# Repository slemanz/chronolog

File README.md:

# Chronolog

## Overview

Chronolog is a temperature data logger built end to end, covering both hardware
and firmware. It records timestamped temperature readings to external flash and
shows live data on an LCD and over Wi-Fi.

📄 [View the schematic](hardware/schematic/chronolog.pdf)

## Repository Structure

- 🔌 **[hardware](hardware/):** KiCad project with schematic, PCB layout and
production files.
- 💾 **Firmware:** coming soon

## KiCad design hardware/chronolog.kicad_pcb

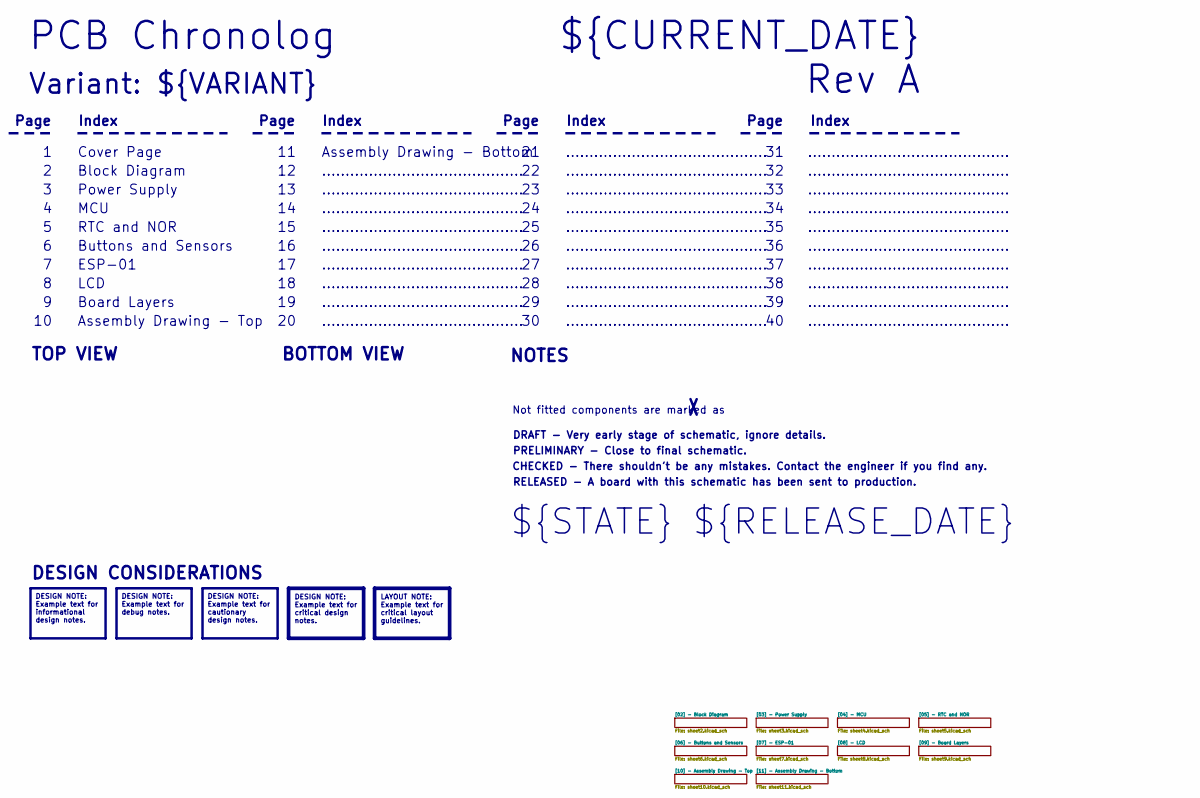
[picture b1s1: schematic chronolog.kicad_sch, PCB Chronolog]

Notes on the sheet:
Page
Not fitted components are marked as
...........................................
Index
RTC and NOR
BOTTOM VIEW
${STATE} ${RELEASE_DATE}
Board Layers
Rev ${REVISION}
DRAFT - Very early stage of schematic, ignore details.
ESP-01
Cover Page
MCU
NOTES
Variant: ${VARIANT}
PRELIMINARY - Close to final schematic.
LCD
DESIGN CONSIDERATIONS
Block Diagram
Assembly Drawing - Bottom
Assembly Drawing - Top
Buttons and Sensors
Power Supply
${CURRENT_DATE}
RELEASED - A board with this schematic has been sent to production.
${TITLE}
CHECKED - There shouldn't be any mistakes. Contact the engineer if you find any.
TOP VIEW
DESIGN NOTE: Example text for debug notes.
DESIGN NOTE: Example text for cautionary design notes.
LAYOUT NOTE: Example text for critical layout guidelines.
DESIGN NOTE: Example text for critical design notes.
DESIGN NOTE: Example text for informational design notes.

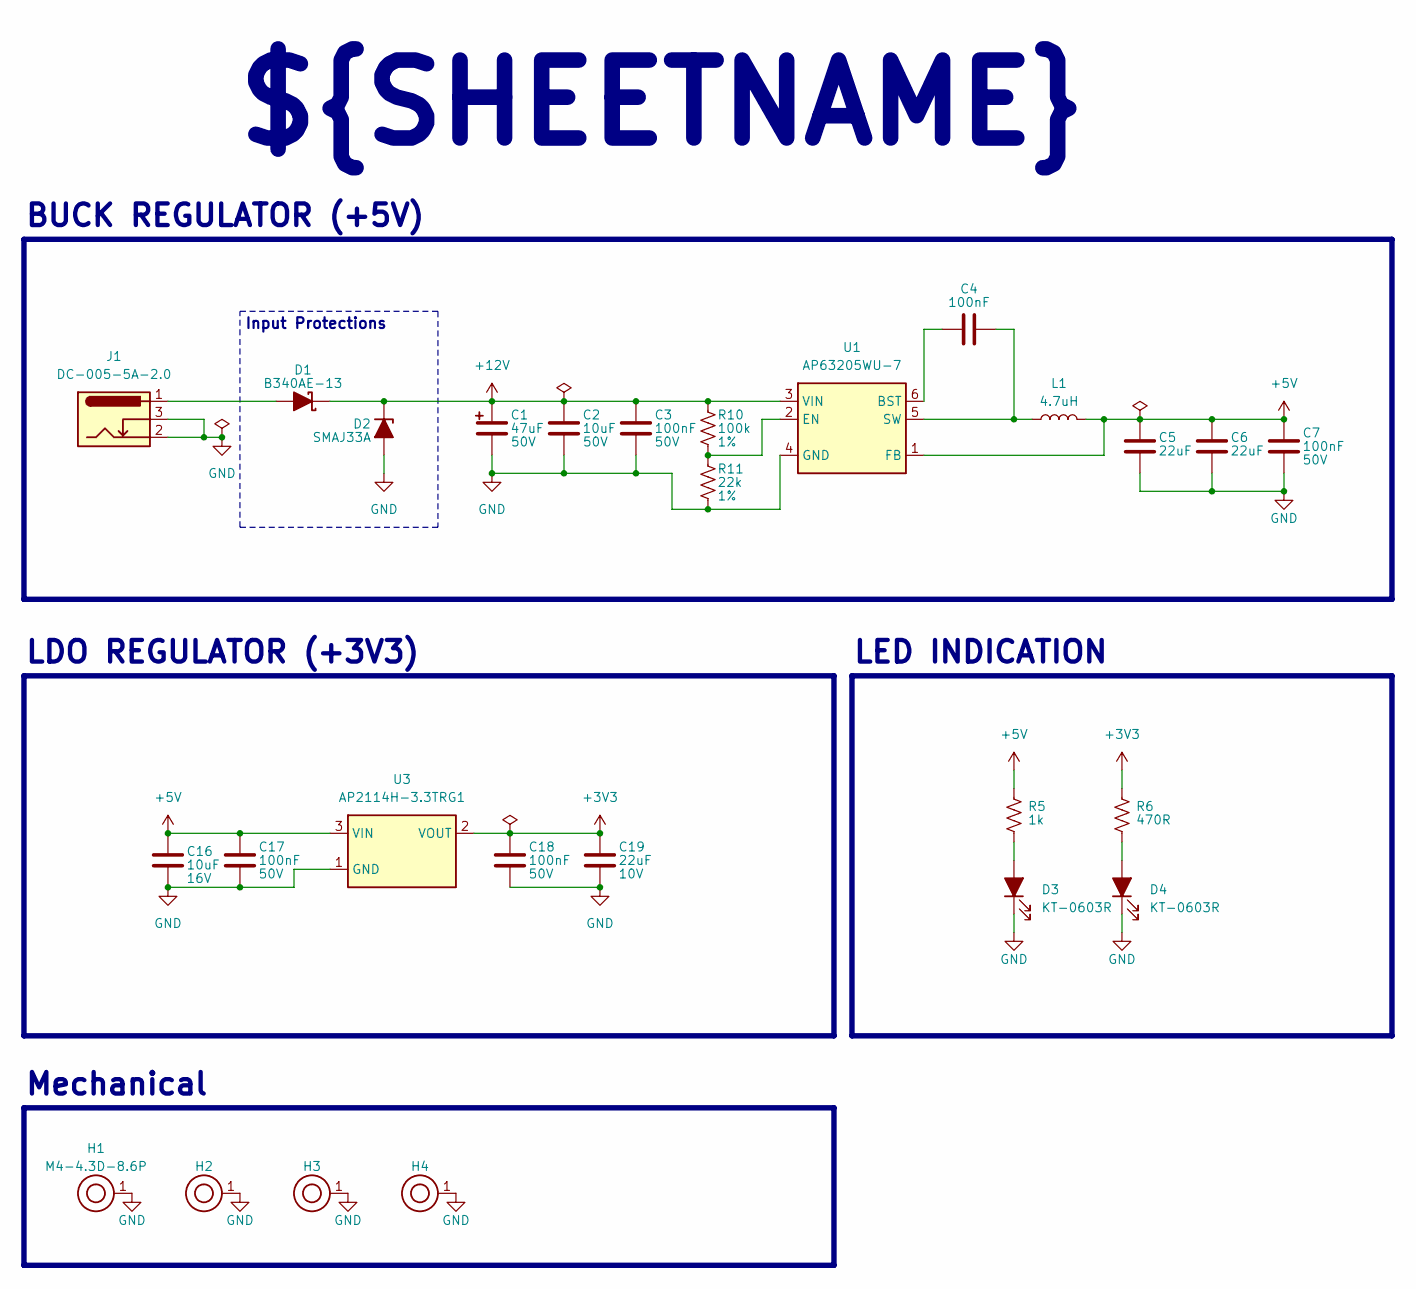
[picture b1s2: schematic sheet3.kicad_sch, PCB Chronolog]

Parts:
C1: 47uF; CP_Elec_6.3x5.8; Tolerance 20%; Voltage 50V; MPN VZT470M1HTT-0606L; LCSC C46682638
C2: 10uF; C_1210_3225Metric; Tolerance 10%; Voltage 50V; MPN GRM32ER71H106KA12L; LCSC C77102
C3, C4, C7, C17, C18: 100nF; C_0603_1608Metric; Tolerance 10%; Voltage 50V; MPN CC0603KRX7R9BB104; LCSC C14663
C5, C6: 22uF; C_1210_3225Metric; Tolerance 10%; Voltage 25V; MPN CL32B226KAJNNNE; LCSC C309062
C16: 10uF; C_0805_2012Metric; Tolerance 10%; Voltage 16V; MPN GRM21BR61C106KE15L; LCSC C77075
C19: 22uF; C_0805_2012Metric; Tolerance 20%; Voltage 10V; MPN GRM21BR61A226ME51L; LCSC C77074
D1: B340AE-13; D_SMA; MPN B340AE-13; LCSC C168859
D2: SMAJ33A; D_SMA; MPN SMAJ33A; LCSC C223988
D3, D4: KT-0603R; LED_0603_1608Metric; MPN KT-0603R; LCSC C2286
H1, H2, H3, H4: M4-4.3D-8.6P; MountingHole_4.3mm_M4_Pad
J1: DC-005-5A-2.0; TH_DC-005-5A-2.0; MPN DC-005-5A-2.0; LCSC C381116
L1: 4.7uH; L_1008_2520Metric; Tolerance 20%; MPN DFE252012F-4R7M=P2; LCSC C668313
R5: 1k; R_0603_1608Metric; Tolerance 1%; MPN 0603WAF1001T5E; LCSC C21190
R6: 470R; R_0603_1608Metric; Tolerance 1%; MPN 0603WAF4700T5E; LCSC C23179
R10: 100k; R_0603_1608Metric; Tolerance 1%; MPN 0603WAF1003T5E; LCSC C25803
R11: 22k; R_0603_1608Metric; Tolerance 1%; MPN 0603WAF2202T5E; LCSC C31850
U1: AP63205WU-7; TSOT-23-6; MPN AP63205WU-7; LCSC C2071056
U3: AP2114H-3.3TRG1; SOT-223-3_TabPin2; MPN AP2114H-3.3TRG1; LCSC C150716

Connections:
+3V3: C18.1, C19.1, R6.1, U3.2 (VOUT); also elsewhere on the board
+5V: C5.1, C6.1, C7.1, C16.1, C17.1, L1.2, R5.1, U1.1 (FB), U3.3 (VIN); also elsewhere on the board
+12V: C1.1, C2.1, C3.1, D1.1 (K), D2.1 (K), R10.1, U1.3 (VIN)
GND: C1.2, C2.2, C3.2, C5.2, C6.2, C7.2, C16.2, C17.2, C18.2, C19.2, D2.2 (A), D3.1 (K), D4.1 (K), H1.1, H2.1, H3.1, H4.1, J1.2, J1.3, R11.2, U1.4 (GND), U3.1 (GND); also elsewhere on the board
unnamed: D1.2 (A), J1.1
unnamed: D3.2 (A), R5.2
unnamed: D4.2 (A), R6.2
unnamed: C4.1, U1.6 (BST)
unnamed: R10.2, R11.1, U1.2 (EN)
unnamed: C4.2, L1.1, U1.5 (SW)

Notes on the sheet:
BUCK REGULATOR (+5V)
LED INDICATION
Input Protections
${SHEETNAME}
LDO REGULATOR (+3V3)
Mechanical

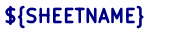
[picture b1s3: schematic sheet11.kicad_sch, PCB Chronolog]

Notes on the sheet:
${SHEETNAME}

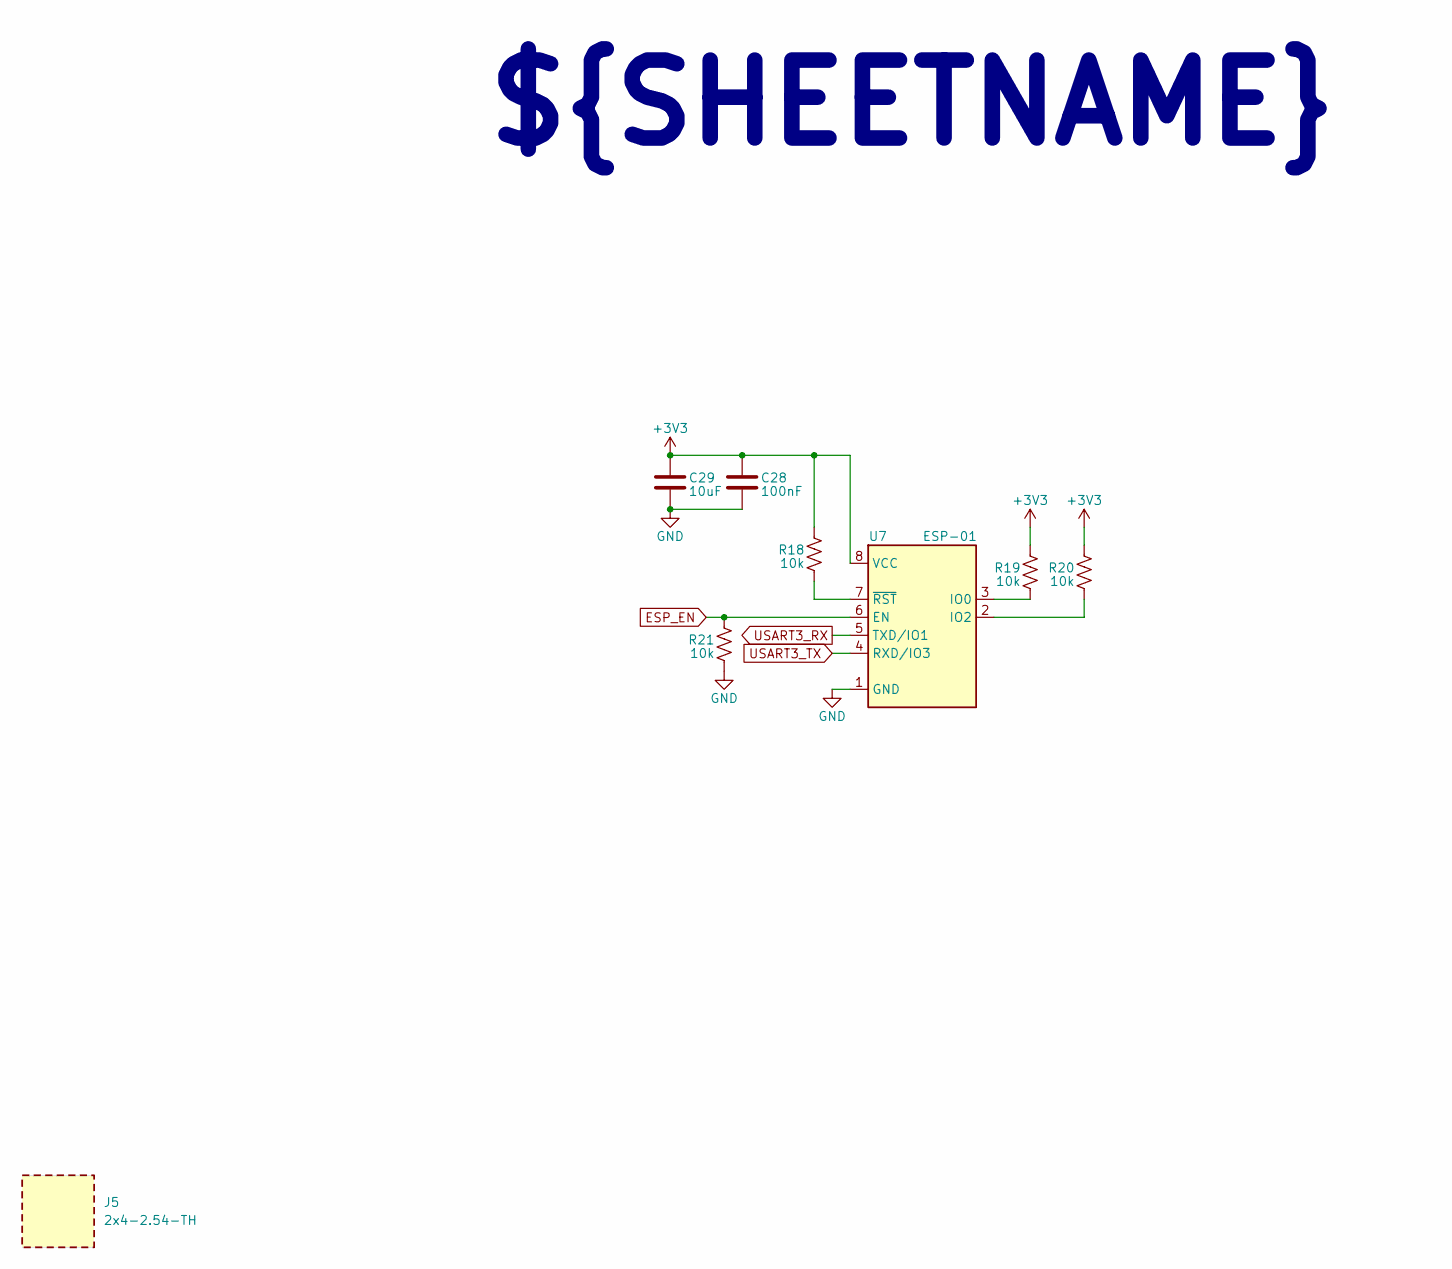
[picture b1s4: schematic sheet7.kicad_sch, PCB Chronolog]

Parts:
C28: 100nF; C_0603_1608Metric; Tolerance 10%; Voltage 50V; MPN CC0603KRX7R9BB104; LCSC C14663
C29: 10uF; C_0805_2012Metric; Tolerance 10%; Voltage 16V; MPN GRM21BR61C106KE15L; LCSC C77075
J5: 2x4-2.54-TH; MPN PM254-2-04-Z-8.5; LCSC C2897405
R18, R19, R20, R21: 10k; R_0603_1608Metric; Tolerance 1%; MPN 0603WAF1002T5E; LCSC C25804
U7: ESP-01; MPN ESP-01; LCSC C503581

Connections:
+3V3: C28.1, C29.1, R18.1, R19.1, R20.1, U7.8 (VCC); also elsewhere on the board
ESP_EN: R21.1, U7.6 (EN); also elsewhere on the board
GND: C28.2, C29.2, R21.2, U7.1 (GND); also elsewhere on the board
unnamed: R19.2, U7.3 (IO0)
unnamed: R20.2, U7.2 (IO2)
unnamed: R18.2, U7.7 (~RST)
USART3_RX: U7.5 (TXD/IO1); also elsewhere on the board
USART3_TX: U7.4 (RXD/IO3); also elsewhere on the board

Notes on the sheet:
${SHEETNAME}

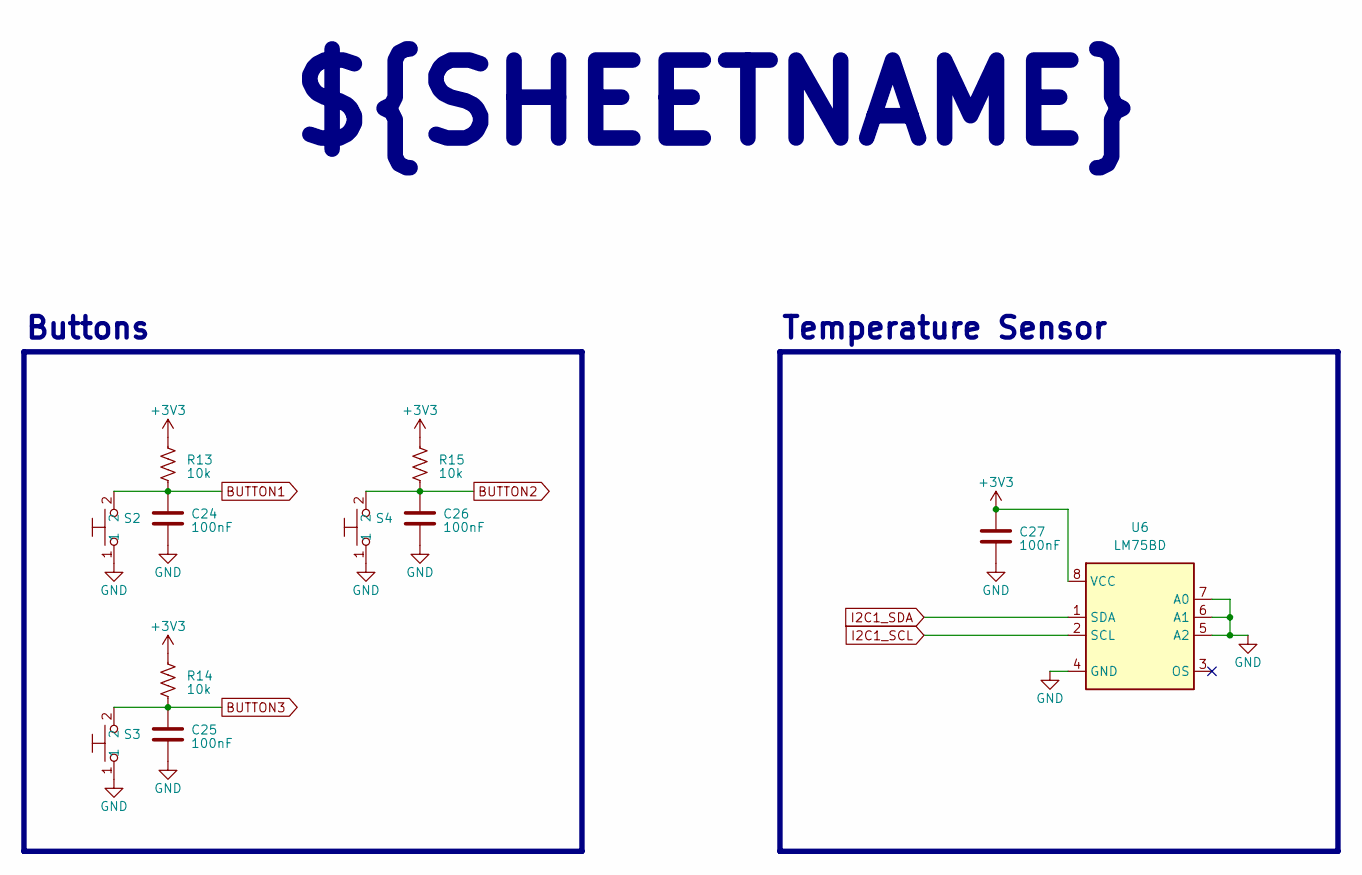
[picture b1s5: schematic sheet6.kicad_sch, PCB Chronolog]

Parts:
C24, C25, C26, C27: 100nF; C_0603_1608Metric; Tolerance 10%; Voltage 50V; MPN CC0603KRX7R9BB104; LCSC C14663
R13, R14, R15: 10k; R_0603_1608Metric; Tolerance 1%; MPN 0603WAF1002T5E; LCSC C25804
S2, S3, S4: TS-1088-AR02016; SW_SPST_TS-1088-xR020; MPN TS-1088-AR02016; LCSC C720477
U6: LM75BD; SOIC-8_3.9x4.9mm_P1.27mm; MPN LM75BD,118; LCSC C34565

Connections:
+3V3: C27.1, R13.1, R14.1, R15.1, U6.8 (VCC); also elsewhere on the board
BUTTON1: C24.1, R13.2, S2.2; also elsewhere on the board
BUTTON2: C26.1, R15.2, S4.2; also elsewhere on the board
BUTTON3: C25.1, R14.2, S3.2; also elsewhere on the board
GND: C24.2, C25.2, C26.2, C27.2, S2.1, S3.1, S4.1, U6.4 (GND), U6.5 (A2), U6.6 (A1), U6.7 (A0); also elsewhere on the board
I2C1_SCL: U6.2 (SCL); also elsewhere on the board
I2C1_SDA: U6.1 (SDA); also elsewhere on the board

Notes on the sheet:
Buttons
Temperature Sensor
${SHEETNAME}

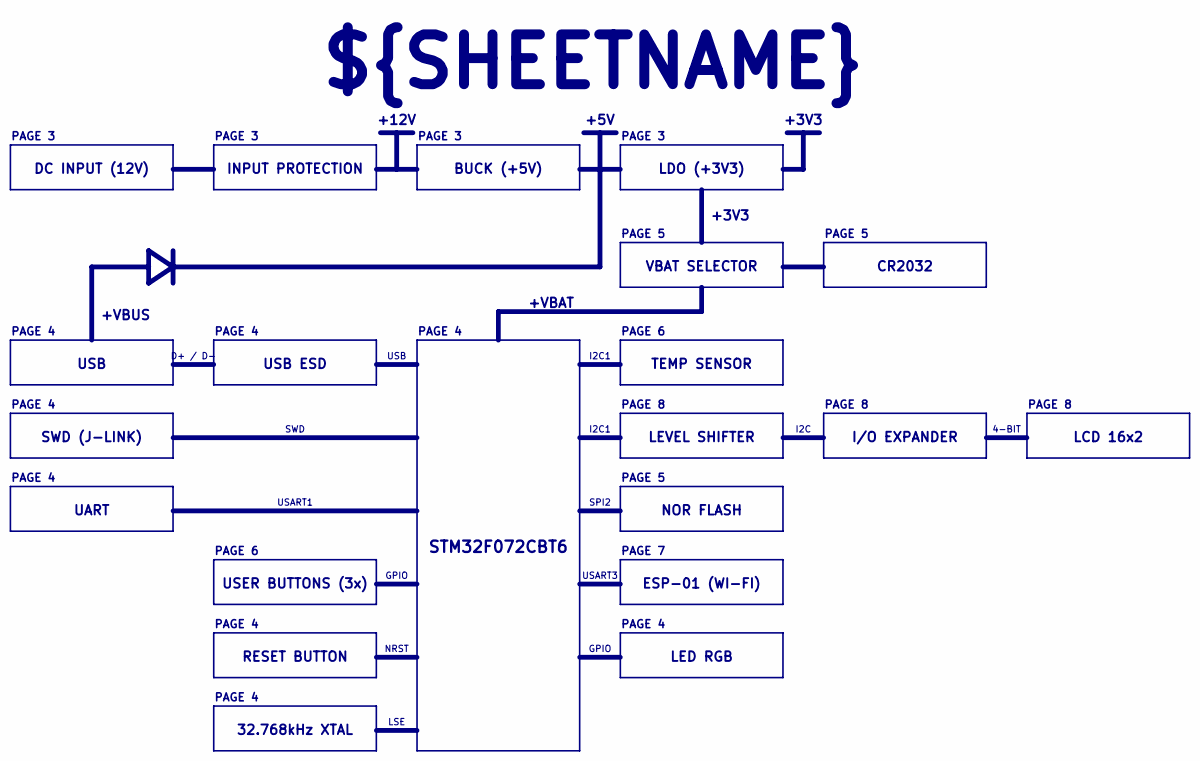
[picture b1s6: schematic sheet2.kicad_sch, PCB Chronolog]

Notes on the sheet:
PAGE 8
PAGE 3
+VBUS
NOR FLASH
SWD (J-LINK)
VBAT SELECTOR
USB ESD
NRST
PAGE 4
PAGE 6
+12V
INPUT PROTECTION
PAGE 5
DC INPUT (12V)
LED RGB
SPI2
LDO (+3V3)
UART
+5V
D+ / D-
+VBAT
CR2032
GPIO
I/O EXPANDER
USART1
+3V3
${SHEETNAME}
PAGE 7
32.768kHz XTAL
ESP-01 (WI-FI)
SWD
TEMP SENSOR
STM32F072CBT6
LSE
USB
USART3
4-BIT
I2C1
LEVEL SHIFTER
RESET BUTTON

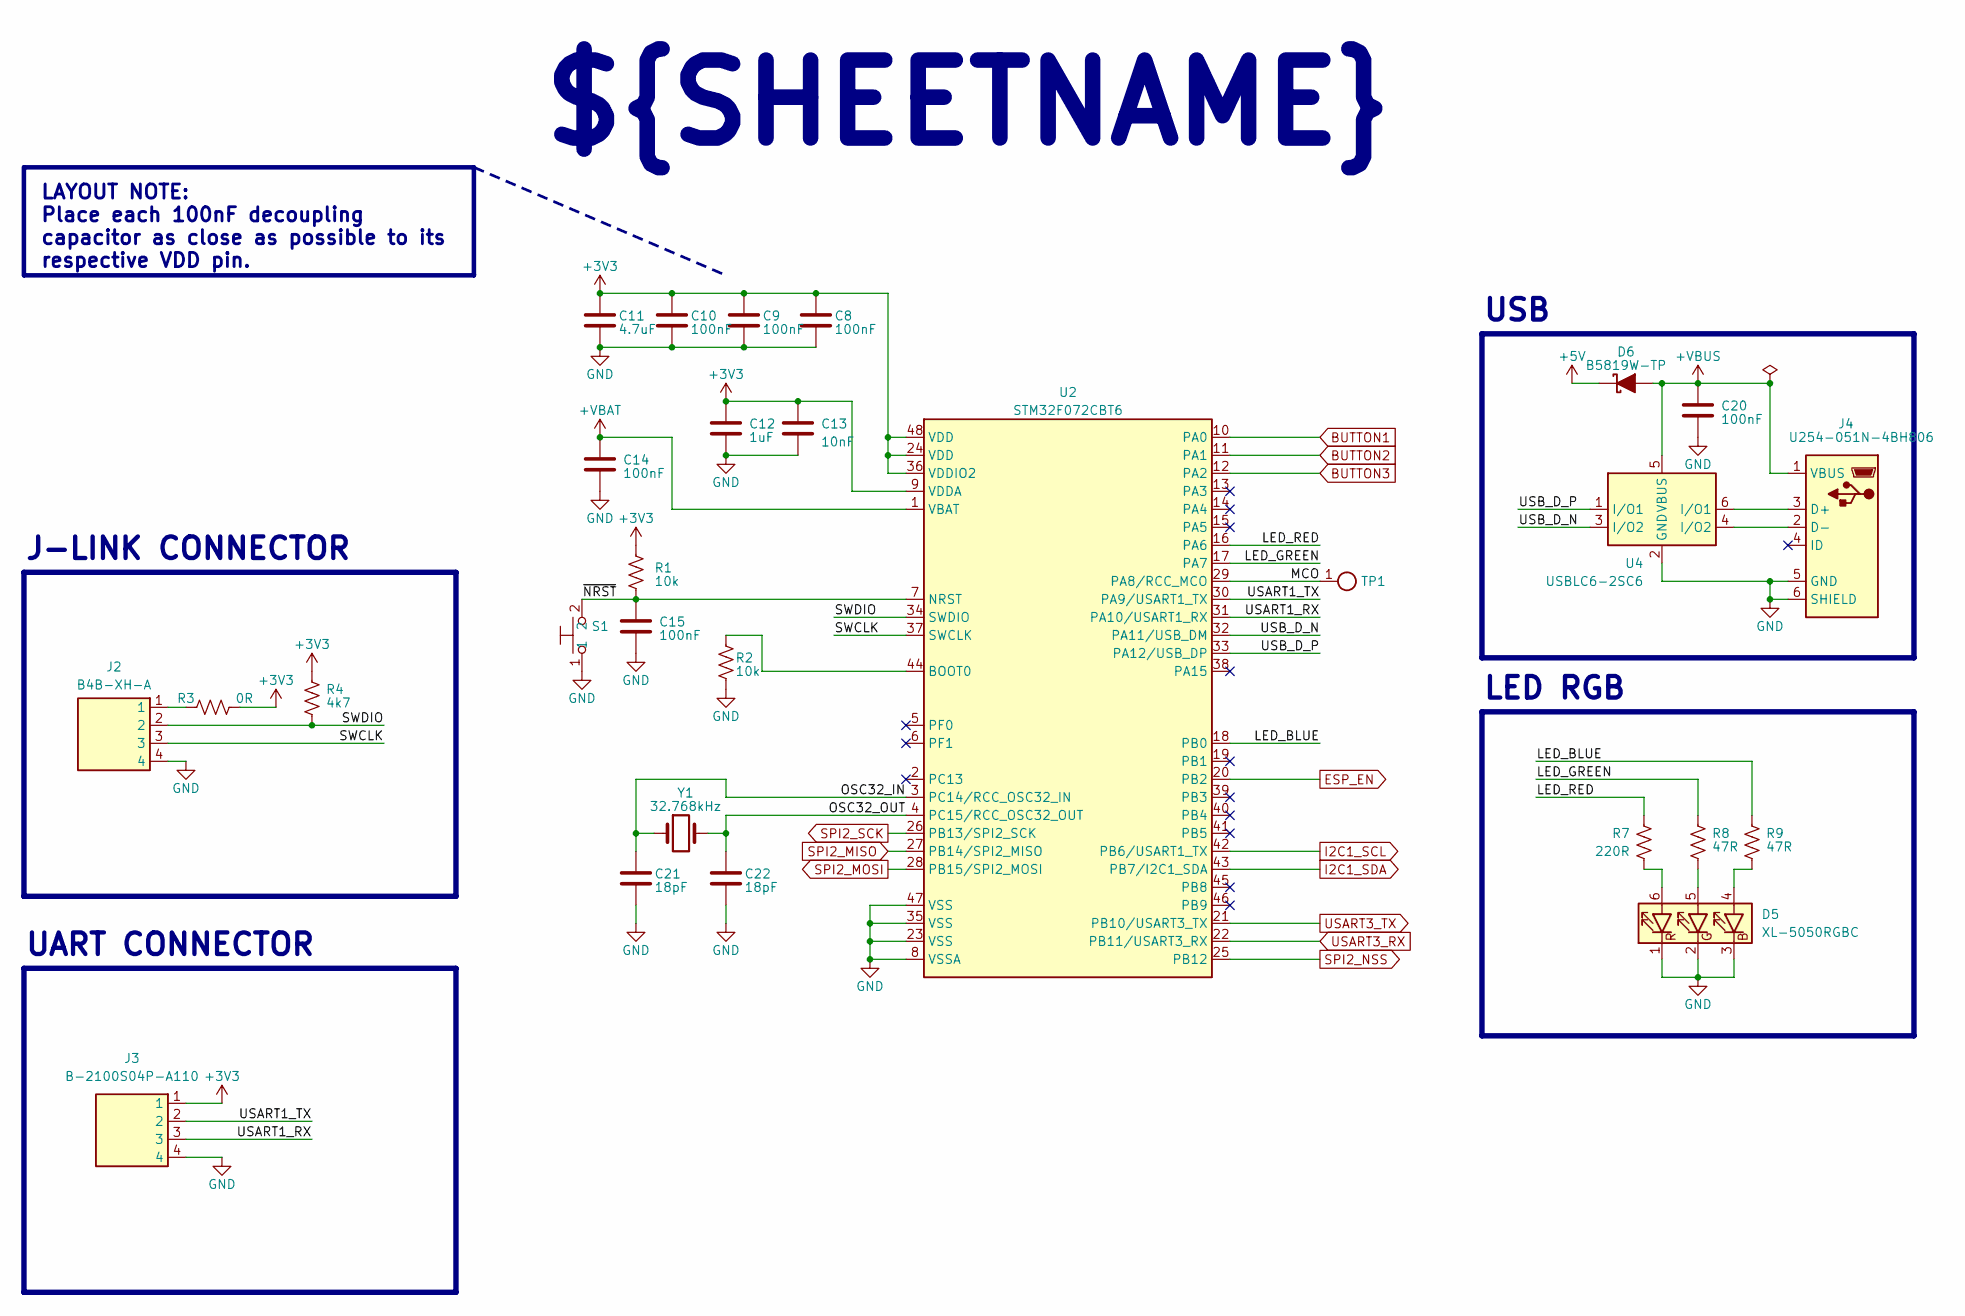
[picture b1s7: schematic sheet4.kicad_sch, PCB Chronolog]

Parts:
C8, C9, C10, C14, C15, C20: 100nF; C_0603_1608Metric; Tolerance 10%; Voltage 50V; MPN CC0603KRX7R9BB104; LCSC C14663
C11: 4.7uF; C_0603_1608Metric; Tolerance 10%; Voltage 16V; MPN GRM188R61C475KE11D; LCSC C77045
C12: 1uF; C_0603_1608Metric; Tolerance 10%; Voltage 25V; MPN GCM188R71E105KA64D; LCSC C85862
C13: 10nF; C_0603_1608Metric; Tolerance 10%; Voltage 50V; MPN 0603B103K500NT; LCSC C57112
C21, C22: 18pF; C_0603_1608Metric; Tolerance 5%; Voltage 50V; MPN CL10C180JB8NNNC; LCSC C1647
D5: XL-5050RGBC; PLCC-6_XL-5050RGBC; MPN XL-5050RGBC; LCSC C2843868
D6: B5819W-TP; D_SOD-123; MPN B5819W-TP; LCSC C84354
J2: B4B-XH-A; JST_XH_B4B-XH-A_1x04_P2.50mm_Vertical; MPN B4B-XH-A(LF)(SN); LCSC C144395
J3: B-2100S04P-A110; PinHeader_1x04_P2.54mm_Vertical; MPN B-2100S04P-A110; LCSC C124378
J4: U254-051N-4BH806; SMD_U254-051N-4BH806; MPN U254-051N-4BH806; LCSC C319170
R1, R2: 10k; R_0603_1608Metric; Tolerance 1%; MPN 0603WAF1002T5E; LCSC C25804
R3: 0R; R_0603_1608Metric; MPN 0603WAF0000T5E; LCSC C21189
R4: 4k7; R_0603_1608Metric; Tolerance 1%; MPN 0603WAF4701T5E; LCSC C23162
R7: 220R; R_0603_1608Metric; Tolerance 1%; MPN 0603WAF2200T5E; LCSC C22962
R8, R9: 47R; R_0603_1608Metric; Tolerance 1%; MPN 0603WAF470JT5E; LCSC C23182
S1: TS-1088-AR02016; SW_SPST_TS-1088-xR020; MPN TS-1088-AR02016; LCSC C720477
TP1: 1.0P-SMD; TestPoint_Pad_D1.0mm
U2: STM32F072CBT6; LQFP-48_7x7mm_P0.5mm; MPN STM32F072CBT6; LCSC C81720
U4: USBLC6-2SC6; SOT-23-6; MPN USBLC6-2SC6; LCSC C7519
Y1: 32.768kHz; Crystal_SMD_3215-2Pin_3.2x1.5mm; MPN Q13FC1350000400; LCSC C32346

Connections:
+3V3: C8.1, C9.1, C10.1, C11.1, C12.1, C13.1, J3.1, R1.1, R3.2, R4.1, U2.9 (VDDA), U2.24 (VDD), U2.36 (VDDIO2), U2.48 (VDD); also elsewhere on the board
+5V: D6.1 (K); also elsewhere on the board
+VBAT: C14.1, U2.1 (VBAT); also elsewhere on the board
+VBUS: C20.1, D6.2 (A), J4.1 (VBUS), U4.5 (VBUS)
/[04] - MCU/LED_BLUE: R9.1, U2.18 (PB0)
/[04] - MCU/LED_GREEN: R8.1, U2.17 (PA7)
/[04] - MCU/LED_RED: R7.1, U2.16 (PA6)
/[04] - MCU/MCO: TP1.1, U2.29 (PA8/RCC_MCO)
/[04] - MCU/OSC32_IN: C21.1, U2.3 (PC14/RCC_OSC32_IN), Y1.1
/[04] - MCU/OSC32_OUT: C22.1, U2.4 (PC15/RCC_OSC32_OUT), Y1.2
/[04] - MCU/SWCLK: J2.3, U2.37 (SWCLK)
/[04] - MCU/SWDIO: J2.2, R4.2, U2.34 (SWDIO)
/[04] - MCU/USART1_RX: J3.3, U2.31 (PA10/USART1_RX)
/[04] - MCU/USART1_TX: J3.2, U2.30 (PA9/USART1_TX)
/[04] - MCU/USB_D_N: U2.32 (PA11/USB_DM), U4.3 (I/O2)
/[04] - MCU/USB_D_P: U2.33 (PA12/USB_DP), U4.1 (I/O1)
/[04] - MCU/~NRST: C15.1, R1.2, S1.2, U2.7 (NRST)
BUTTON1: U2.10 (PA0); also elsewhere on the board
BUTTON2: U2.11 (PA1); also elsewhere on the board
BUTTON3: U2.12 (PA2); also elsewhere on the board
ESP_EN: U2.20 (PB2); also elsewhere on the board
GND: C8.2, C9.2, C10.2, C11.2, C12.2, C13.2, C14.2, C15.2, C20.2, C21.2, C22.2, D5.1 (RK), D5.2 (GK), D5.3 (BK), J2.4, J3.4, J4.5 (GND), J4.6 (SHIELD), R2.2, S1.1, U2.8 (VSSA), U2.23 (VSS), U2.35 (VSS), U2.47 (VSS), U4.2 (GND); also elsewhere on the board
I2C1_SCL: U2.42 (PB6/USART1_TX); also elsewhere on the board
I2C1_SDA: U2.43 (PB7/I2C1_SDA); also elsewhere on the board
unnamed: D5.4 (BA), R9.2
unnamed: D5.5 (GA), R8.2
unnamed: D5.6 (RA), R7.2
unnamed: J2.1, R3.1
unnamed: J4.3 (D+), U4.6 (I/O1)
unnamed: J4.2 (D-), U4.4 (I/O2)
unnamed: R2.1, U2.44 (BOOT0)
SPI2_MISO: U2.27 (PB14/SPI2_MISO); also elsewhere on the board
SPI2_MOSI: U2.28 (PB15/SPI2_MOSI); also elsewhere on the board
SPI2_NSS: U2.25 (PB12); also elsewhere on the board
SPI2_SCK: U2.26 (PB13/SPI2_SCK); also elsewhere on the board
USART3_RX: U2.22 (PB11/USART3_RX); also elsewhere on the board
USART3_TX: U2.21 (PB10/USART3_TX); also elsewhere on the board

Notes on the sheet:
LED RGB
USB
${SHEETNAME}
J-LINK CONNECTOR
UART CONNECTOR
LAYOUT NOTE: Place each 100nF decoupling capacitor as close as possible to its respective VDD pin.

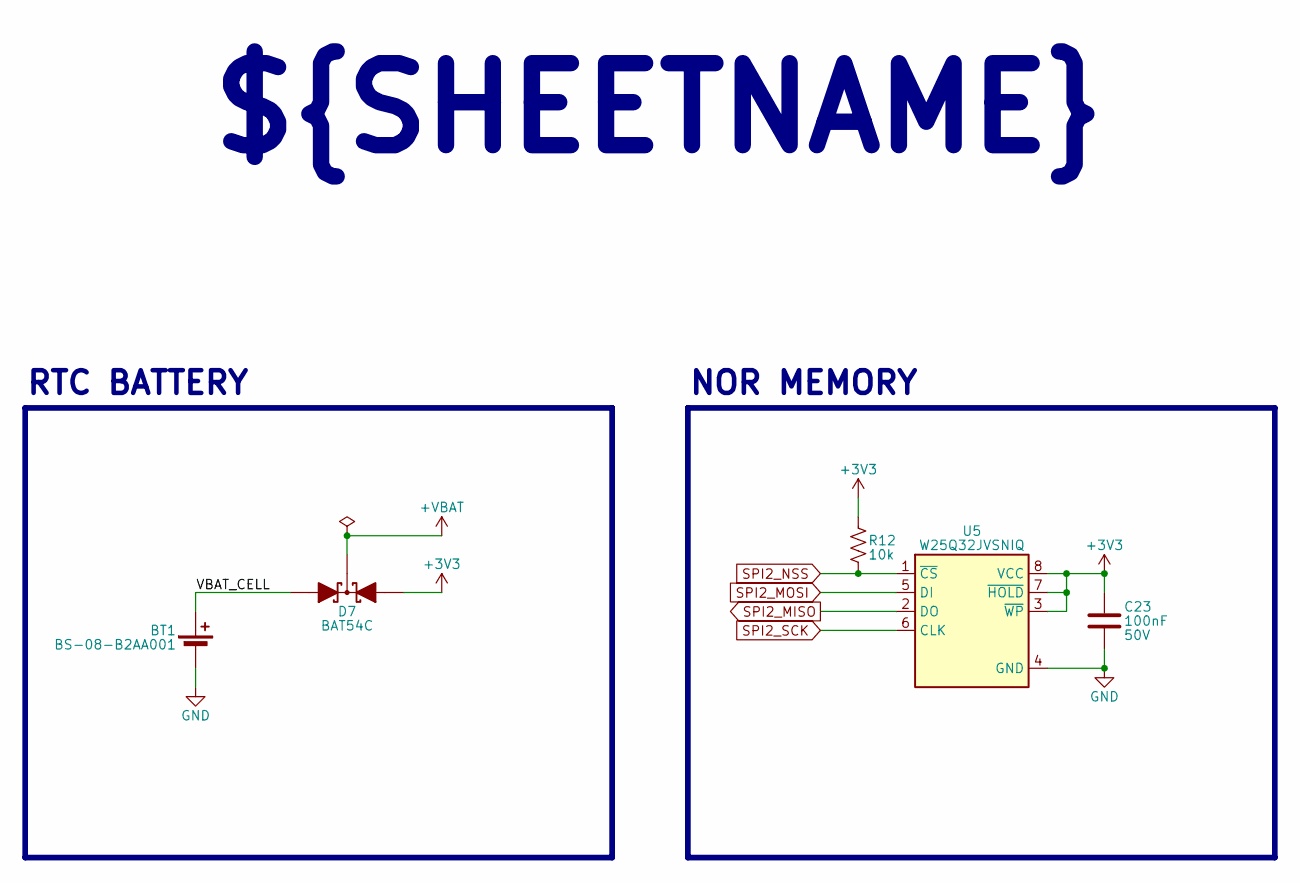
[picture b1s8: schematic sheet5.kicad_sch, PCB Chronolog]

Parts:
BT1: BS-08-B2AA001; SMD_BS-08-B2AA001; MPN BS-08-B2AA001; LCSC C964777
C23: 100nF; C_0603_1608Metric; Tolerance 10%; Voltage 50V; MPN CC0603KRX7R9BB104; LCSC C14663
D7: BAT54C; SOT-23; MPN BAT54C; LCSC C2135
R12: 10k; R_0603_1608Metric; Tolerance 1%; MPN 0603WAF1002T5E; LCSC C25804
U5: W25Q32JVSNIQ; SOIC-8_3.9x4.9mm_P1.27mm; MPN W25Q32JVSNIQ; LCSC C5355146

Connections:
+3V3: C23.1, D7.1 (A1), R12.1, U5.3 (~WP), U5.7 (~HOLD), U5.8 (VCC); also elsewhere on the board
+VBAT: D7.3 (K); also elsewhere on the board
/[05] - RTC and NOR/VBAT_CELL: BT1.1 (+), D7.2 (A2)
GND: BT1.2 (-), C23.2, U5.4 (GND); also elsewhere on the board
SPI2_MISO: U5.2 (DO); also elsewhere on the board
SPI2_MOSI: U5.5 (DI); also elsewhere on the board
SPI2_NSS: R12.2, U5.1 (~CS); also elsewhere on the board
SPI2_SCK: U5.6 (CLK); also elsewhere on the board

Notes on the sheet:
${SHEETNAME}
NOR MEMORY
RTC BATTERY

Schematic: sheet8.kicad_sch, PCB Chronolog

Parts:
C30, C31: 100nF; C_0603_1608Metric; Tolerance 10%; Voltage 50V; MPN CC0603KRX7R9BB104; LCSC C14663
J6: 1x16-2.54-TH; MPN KH-2.54FH-1X16P-H8.5; LCSC C2905421
P1: 1x16-2.54-TH; MPN B-2100S16P-A110; LCSC C49423290
Q1, Q2: BSS138; SOT-23; MPN BSS138; LCSC C52895
Q3: BC817-40LT1G; SOT-23; MPN BC817-40LT1G; LCSC C94412
R16, R17, R22, R25: 4k7; R_0603_1608Metric; Tolerance 1%; MPN 0603WAF4701T5E; LCSC C23162
R23: 1k; R_0603_1608Metric; Tolerance 1%; MPN 0603WAF1001T5E; LCSC C21190
R24: 10k; TH_3362P; Tolerance 10%; MPN 3362P-1-103LF; LCSC C58159
R26: 12R; R_0805_2012Metric; Tolerance 1%; MPN 0805W8F120JT5E; LCSC C17445
U8: WC1602A; MPN WC1602A; LCSC C5329588
U9: PCF8574T; SOIC-16W_7.5x10.3mm_P1.27mm; MPN PCF8574T; LCSC C7605

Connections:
+3V3: Q1.1 (G), Q2.1 (G), R16.1, R17.1; also elsewhere on the board
+5V: C30.1, C31.1, R22.1, R24.3, R25.1, R26.1, U8.2 (VDD), U9.16 (VDD); also elsewhere on the board
/[08] - LCD/LCD_BL: R23.1, U9.7 (P3)
/[08] - LCD/LCD_D4: U8.11 (D4), U9.9 (P4)
/[08] - LCD/LCD_D5: U8.12 (D5), U9.10 (P5)
/[08] - LCD/LCD_D6: U8.13 (D6), U9.11 (P6)
/[08] - LCD/LCD_D7: U8.14 (D7), U9.12 (P7)
/[08] - LCD/LCD_EN: U8.6 (E), U9.6 (P2)
/[08] - LCD/LCD_RS: U8.4 (RS), U9.4 (P0)
/[08] - LCD/LCD_RW: U8.5 (R/W), U9.5 (P1)
/[08] - LCD/LCD_SCL: Q1.3 (D), R25.2, U9.14 (SCL)
/[08] - LCD/LCD_SDA: Q2.3 (D), R22.2, U9.15 (SDA)
GND: C30.2, C31.2, Q3.2 (E), R24.1, U8.1 (VSS), U9.1 (A0), U9.2 (A1), U9.3 (A2), U9.8 (GND); also elsewhere on the board
I2C1_SCL: Q1.2 (S), R17.2; also elsewhere on the board
I2C1_SDA: Q2.2 (S), R16.2; also elsewhere on the board
unnamed: Q3.1 (B), R23.2
unnamed: Q3.3 (C), U8.16 (LED(-))
unnamed: R26.2, U8.15 (LED(+))
unnamed: R24.2, U8.3 (VO)

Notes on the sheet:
${SHEETNAME}

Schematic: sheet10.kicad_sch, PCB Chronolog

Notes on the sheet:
${SHEETNAME}

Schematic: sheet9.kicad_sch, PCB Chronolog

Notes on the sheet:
IN1
${SHEETNAME}
BOTTOM
TOP
IN2
DESIGN NOTE: All layers are viewed from the top side of the board (not mirrored).

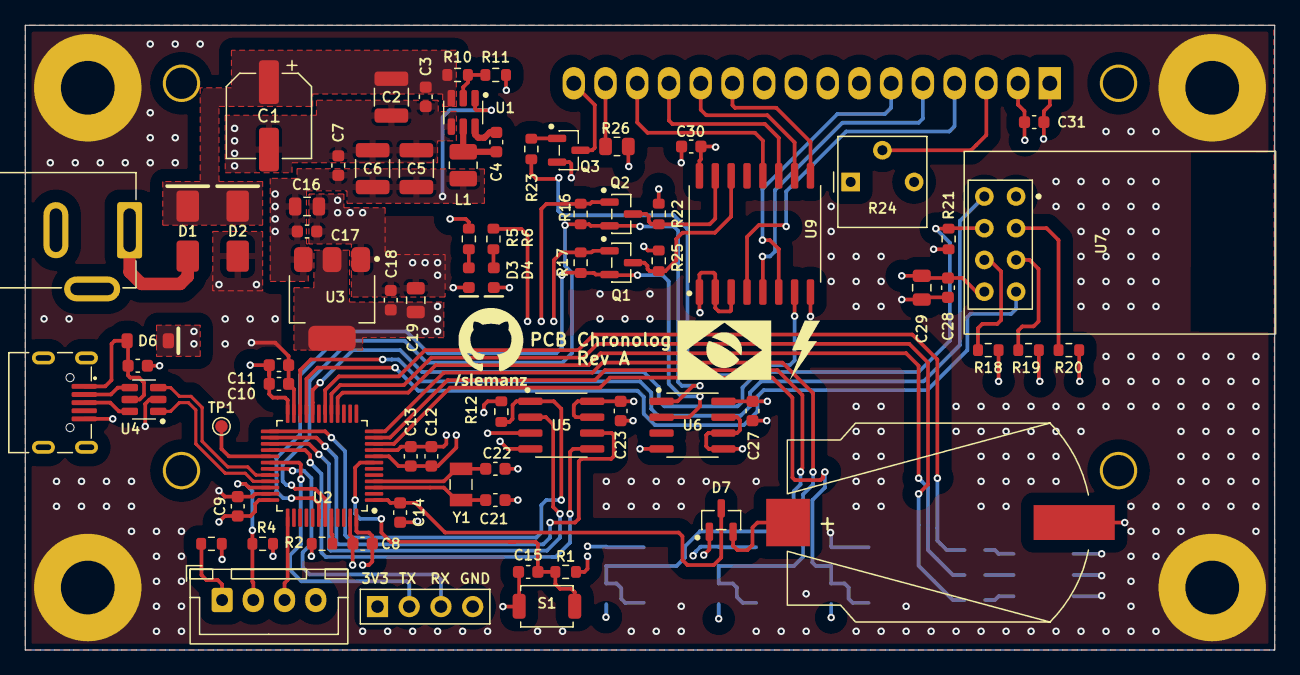
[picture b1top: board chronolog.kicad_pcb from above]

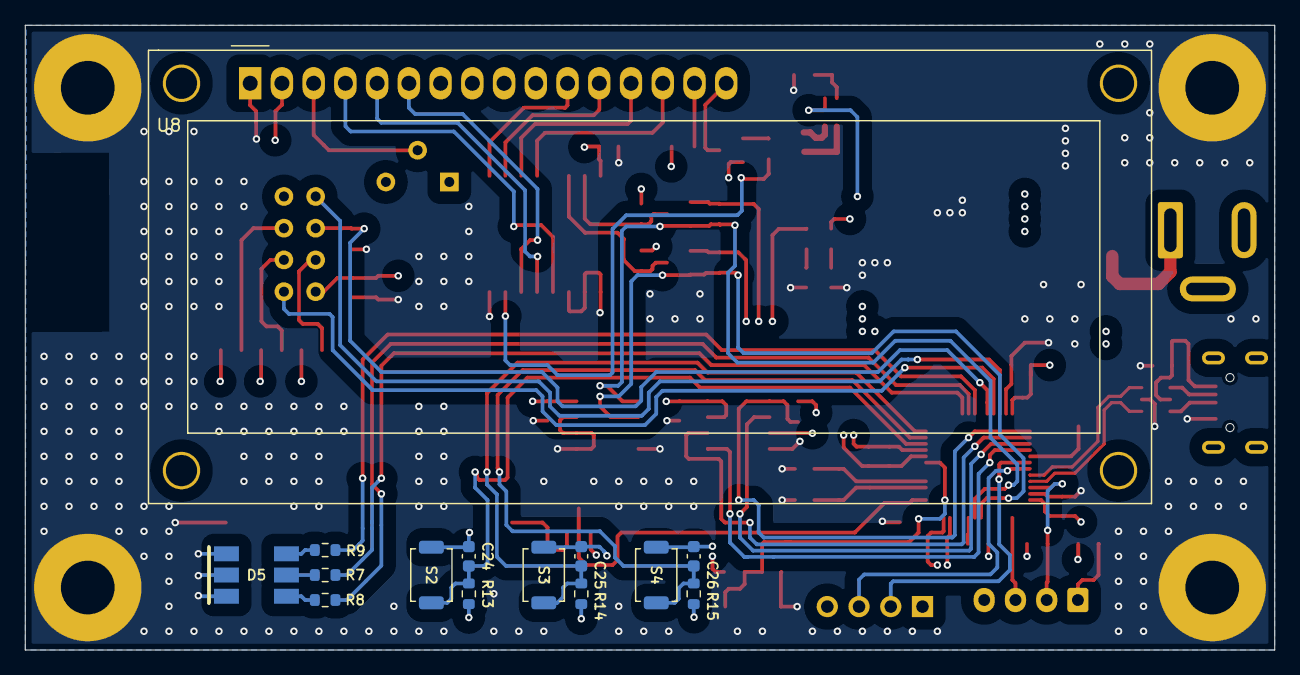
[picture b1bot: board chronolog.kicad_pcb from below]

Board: 4 copper layers, 100.0 x 50.0 mm, 92 parts (14 on the bottom side), 62 nets.

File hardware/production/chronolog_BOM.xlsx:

|  |  |  | BILL OF MATERIALS
 |  |  |  | PCB Chronolog
Designed by: |  | William Sleman |  | Revision: | A
Report Date: |  | 10-OCT-2026 |  | Total parts: | 90
# | Reference | Qty | Description | MPN | LCSC | Package | Unit Price | Total
1 | BT1 | 1 | BATTERY HOLDER COIN CR2032 SMD | BS-08-B2AA001 | C964777 | SMD
2 | C1 | 1 | CAP ALUM 47uF 20% 35V SMD | VZT470M1HTT-0606L | C46682638 | D6.3x5.8
3 | C2 | 1 | CAP CER 10uF 50V X7R 1210 | GRM32ER71H106KA12L | C77102 | 1210
4 | C3, C4, C7, C8, C9, C10, C14, C15, C17, C18, C20, C23, C24, C25, C26, C27, C28,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 | 19 | CAP CER 100nF 50V X7R 0603 | CC0603KRX7R9BB104 | C14663 | 0603
5 | C5, C6 | 2 | CAP CER 22uF 25V X7R 1210 | CL32B226KAJNNNE | C309062 | 1210
6 | C11 | 1 | CAP CER 4.7uF 16V X5R 0603 | GRM188R61C475KE11D | C77045 | 0603
7 | C12 | 1 | CAP CER 1uF 25V X7R 0603 | GCM188R71E105KA64D | C85862 | 0603
8 | C13 | 1 | CAP CER 1nF 50V X7R 0603 | 0603B103K500NT | C57112 | 0603
9 | C16, C29 | 2 | CAP CER 10uF 16V X5R 0805 | GRM21BR61C106KE15L | C77075 | 0805
10 | C19 | 1 | CAP CER 22uF 10V X5R 0805 | GRM21BR61A226ME51L | C77074 | 0805
11 | C21, C22 | 2 | CAP CER 18pF 50V C0G 0603 | CL10C180JB8NNNC | C1647 | 0603
12 | D1 | 1 | DIODE SCHOTTKY 40V 3A SMA | B340AE-13 | C168859 | SMA(DO-214AC)
13 | D2 | 1 | TVS DIODE 33VWM 53.3VC DO214AC | SMAJ33A | C223988 | SMA(DO-214AC)
14 | D3, D4 | 2 | LED RED 620-630nm 2V 20mA 0603 | KT-0603R | C2286 | 0603
15 | D5 | 1 | TOP LED 5050 RGB SMD | XL-5050RGBC | C2843868 | PLCC-6
16 | D6 | 1 | DIODE SCHOTTKY 40V SOD-123 | B5819W-TP | C84354 | SOD-123
17 | D7 | 1 | DIODE ARR SCHOTT 30V 200MA SOT23 | BAT54C | C2135 | SOT-23
18 | J1 | 1 | CONN PWR JACK TH R/A | DC-005-5A-2.0 | C381116 | TH
19 | J2 | 1 | CONN HEADER JST XH 4POS 2.50mm TH | B4B-XH-A(LF)(SN) | C144395 | TH
20 | J3 | 1 | CONN HEADER MALE VERT 4POS 2.54MM | B-2100S04P-A110 | C124378 | TH
21 | J4 | 1 | CONN RCPT USB MICRO-B 5POS SMD | U254-051N-4BH806 | C319170 | SMD
22 | J5 | 1 | CONN SOCKET 8POS 2.54mm DUAL ROW TH | PM254-2-04-Z-8.5 | C2897405 | TH
23 | J6 | 1 | CONN SOCKET 16POS 2.54mm SINGLE ROW TH | KH-2.54FH-1X16P-H8.5 | C2905421 | TH
24 | L1 | 1 | FIXED IND 4.7uH 1.5A ISAT 2.1A 190mΩ 1008 | DFE252012F-4R7M=P2 | C668313 | 1008
25 | P1 | 1 | CONN HEADER MALE VERT 16POS 2.54MM | B-2100S16P-A110 | C49423290 | TH
26 | Q1, Q2 | 2 | MOSFET N-CH 50V 220mA 3.5R SOT-23 | BSS138 | C52895 | SOT-23
27 | Q3 | 1 | TRANS NPN 45V 500mA SOT-23 | BC817-40LT1G | C94412 | SOT-23
28 | R1, R2, R12, R13, R14, R15, R18, R19, R20, R21 | 10 | RES 10kΩ ±1% 100mW 0603 | 0603WAF1002T5E | C25804 | 0603
29 | R3 | 1 | RES 0Ω 100mW 0603 | 0603WAF0000T5E | C21189 | 0603
30 | R4, R16, R17, R22, R25 | 5 | RES 4.7kΩ ±1% 100mW 0603 | 0603WAF4701T5E | C23162 | 0603
31 | R5, R23 | 2 | RES 1kΩ ±1% 100mW 0603 | 0603WAF1001T5E | C21190 | 0603
32 | R6 | 1 | RES 470Ω ±1% 100mW 0603 | 0603WAF4700T5E | C23179 | 0603
33 | R7 | 1 | RES 220Ω ±1% 100mW 0603 | 0603WAF2200T5E | C22962 | 0603
34 | R8, R9 | 2 | RES 47Ω ±1% 100mW 0603 | 0603WAF470JT5E | C23182 | 0603
35 | R10 | 1 | RES 100kΩ ±1% 100mW 0603 | 0603WAF1003T5E | C25803 | 0603
36 | R11 | 1 | RES 22kΩ ±1% 100mW 0603 | 0603WAF2202T5E | C31850 | 0603
37 | R24 | 1 | TRIMMER 10K OHM 0.5W PC PIN TOP | 3362P-1-103LF | C58159 | TH
38 | R26 | 1 | RES 12Ω ±1% 125mW 0805 | 0805W8F120JT5E | C17445 | 0805
39 | S1, S2, S3, S4 | 4 | SWITCH TACTILE SPST SMD | TS-1088-AR02016 | C720477 | SMD
40 | U1 | 1 | IC REG BUCK 5V 2A 3.8V-32V TSOT-23-6 | AP63205WU-7 | C2071056 | TSOT-23-6
41 | U2 | 1 | IC MCU 32BIT 128KB FLASH 48LQFP | STM32F072CBT6 | C81720 | LQFP-48
42 | U3 | 1 | IC REG LDO 3.3V 1A 2.5V-6V SOT-223 | AP2114H-3.3TRG1 | C150716 | SOT-223
43 | U4 | 1 | TVS DIODE 5.25VWM 17VC SOT23-6 | USBLC6-2SC6 | C7519 | SOT-23-6
44 | U5 | 1 | IC FLASH 32MBIT SPI/QUAD 8SOIC | W25Q32JVSNIQ | C5355146 | SOIC-8
45 | U6 | 1 | SENSOR DIGITAL -55C-125C 8SO | LM75BD,118 | C34565 | SOIC-8
46 | U7 | 1 | ESP8266 WI-FI IOT MODULE | ESP-01 | C503581 | MOD
47 | U8 | 1 | LCD CHARACTER DISPLAY MODULE 16x2 | WC1602A | C5329588 | MOD
48 | U9 | 1 | IC EXPANDER 100KHZ I2C 16SO | PCF8574T | C7605 | SOIC-16W
49 | Y1 | 1 | CRYSTAL 32.7680KHZ 12.5PF SMD | Q13FC1350000400 | C32346 | SMD-3215
 | TOTAL
Red text = DNP (Do Not Populate). Parts excluded from the BOM in KiCad are not 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
